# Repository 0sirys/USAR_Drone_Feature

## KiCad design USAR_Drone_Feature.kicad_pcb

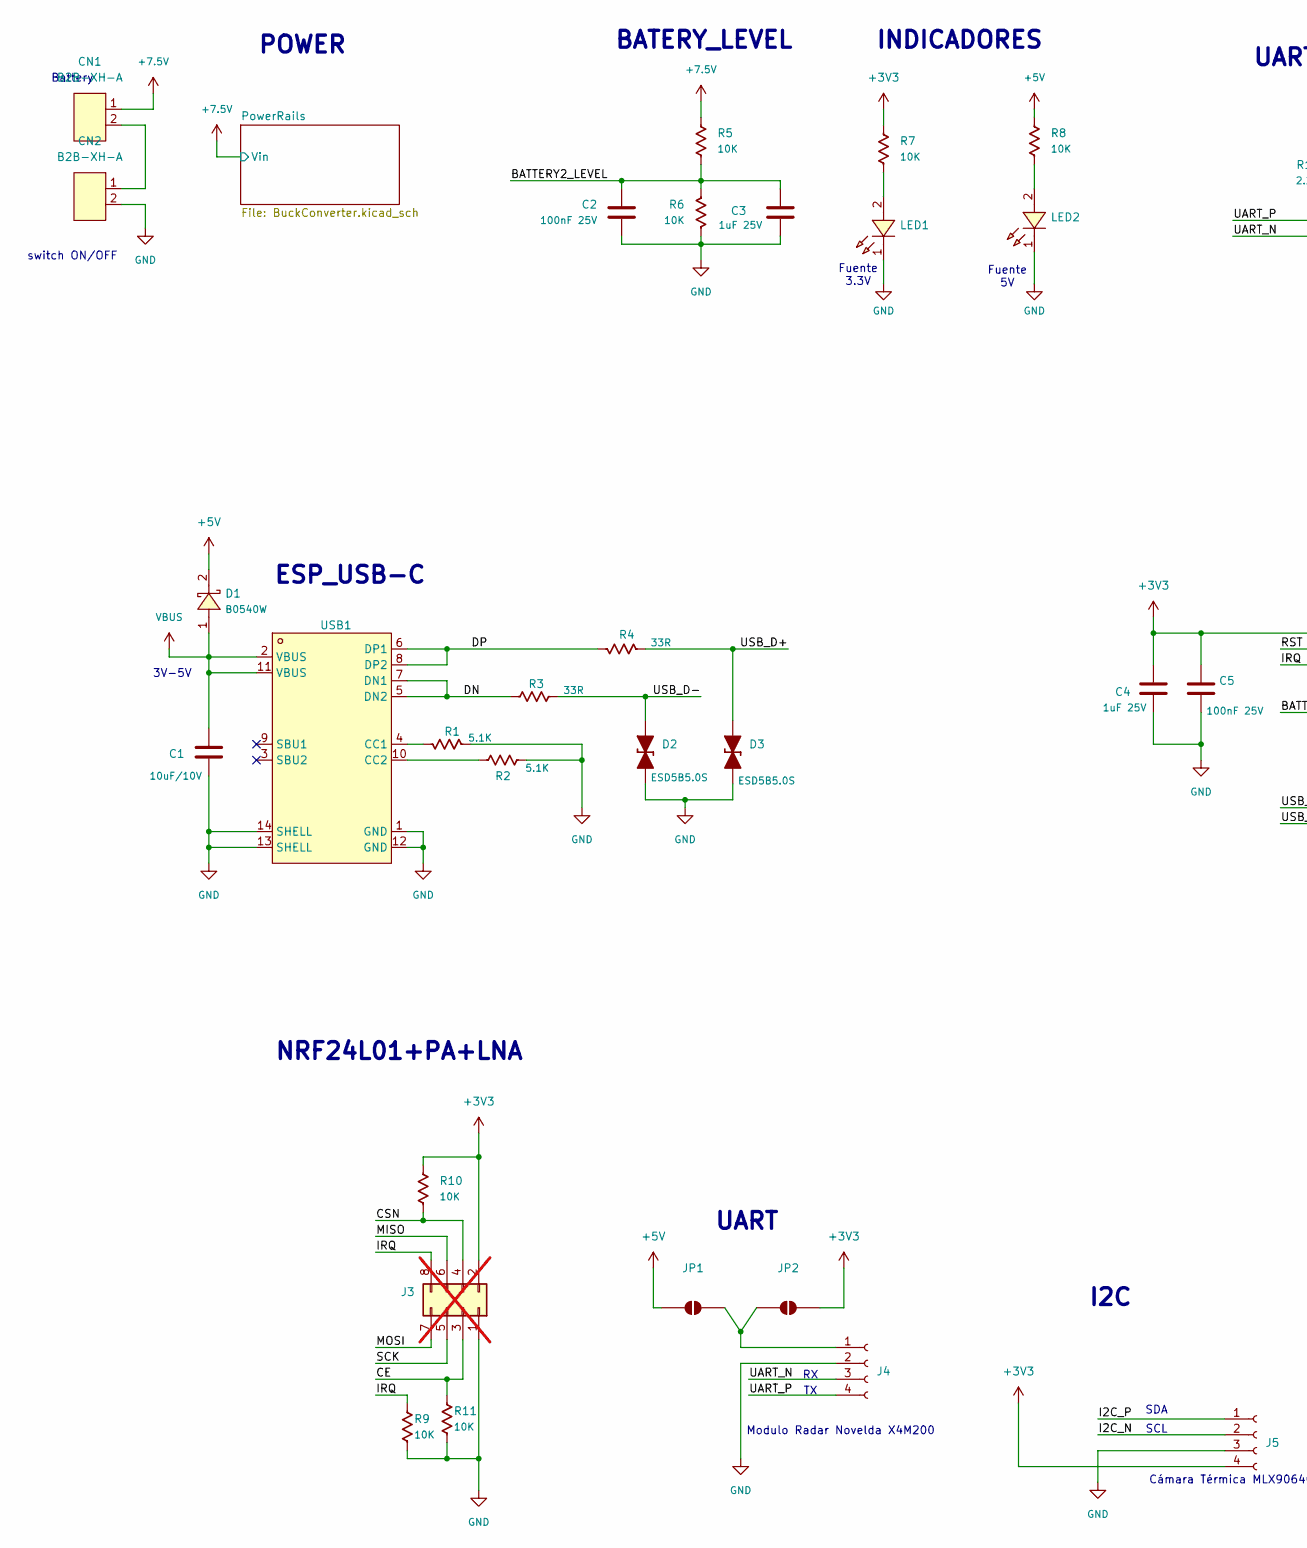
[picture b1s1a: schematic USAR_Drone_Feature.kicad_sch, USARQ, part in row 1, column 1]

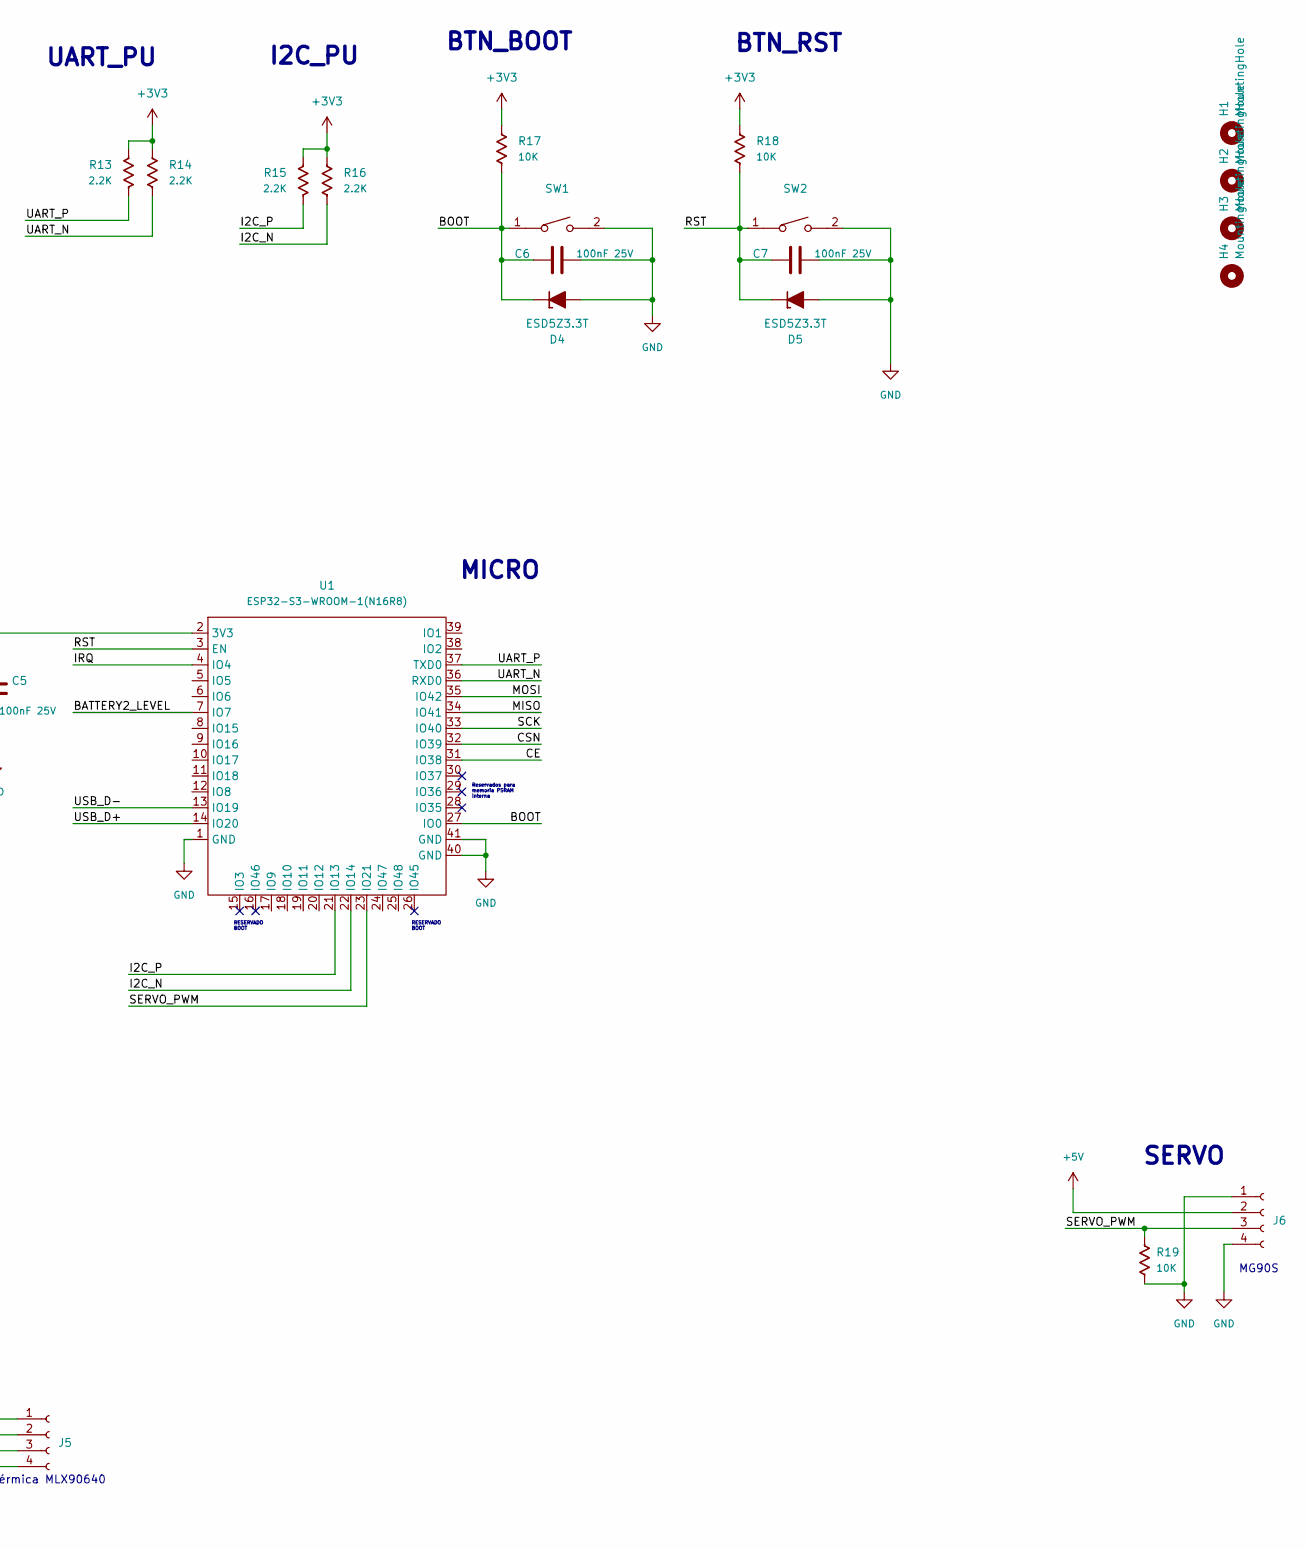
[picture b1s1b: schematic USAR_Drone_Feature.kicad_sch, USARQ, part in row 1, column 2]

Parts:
C1: 10uF/10V; C_0805_2012Metric; LCSC Part C326595
C2, C5, C6, C7: 100nF 25V; C_0603_1608Metric; LCSC Part C14663
C3, C4: 1uF 25V; C_0805_2012Metric; LCSC Part 5370002
CN1, CN2: B2B-XH-A; CONN-TH_B2B-XH-A-LF-SN; MPN B2B-XH-A(LF)(SN); LCSC Part C158012
D1: B0540W; SOD-123_L2.7-W1.6-LS3.7-FD; MPN B0540W; LCSC Part C7420325
D2, D3: ESD5B5.0S; D_SOD-523; LCSC Part C2936975
D4, D5: ESD5Z3.3T; D_SOD-523; LCSC Part C61148
H1, H2, H3, H4: MountingHole; MountingHole_2.5mm
J3: Conn_02x04_Odd_Even; PinHeader_2x04_P2.54mm_Vertical; not fitted
J4, J5, J6: Conn_01x04_Socket; CONN-TH_B4B-PH-K-S; LCSC Part C144395
JP1, JP2: SolderJumper_2_Open; Jumper_2_NO
LED1, LED2: XL-1608SURC-06; LED0603-RD_RED; MPN XL-1608SURC-06; LCSC Part C965799
R1, R2: 5.1K; R_0603_1608Metric; LCSC Part C125891
R3, R4: 33R; R_0603_1608Metric; LCSC Part C108407
R5, R6, R7, R8, R9, R10, R11, R17, R18, R19: 10K; R_0603_1608Metric; LCSC Part C860067
R13, R14, R15, R16: 2.2K; R_0603_1608Metric; LCSC Part C113303
SW1, SW2: TS-1088-AR02016; SW-SMD_L3.9-W3.0-P4.45; MPN TS-1088-AR02016; LCSC Part C720477
U1: ESP32-S3-WROOM-1(N16R8); WIRELM-SMD_ESP32-S3-WROOM-1; LCSC Part C2913202
USB1: TYPE-C 16PIN 2MD; USB-C-SMD_TYPE-C-6PIN-2MD-073; MPN TYPE-C 16PIN 2MD(073); LCSC Part C2765186

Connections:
+3V3: C4.1, C5.1, J3.2, J5.4, JP2.2 (B), R7.1, R10.1, R13.1, R14.1, R15.1, R16.1, R17.1, R18.1, U1.2 (3V3); also elsewhere on the board
+5V: D1.2, J6.2, JP1.1 (A), R8.1; also elsewhere on the board
+7.5V: CN1.1, R5.1; also elsewhere on the board
/BATTERY2_LEVEL: C2.1, C3.1, R5.2, R6.1, U1.7 (IO7)
/BOOT: C6.1, D4.1 (K), R17.2, SW1.1, U1.27 (IO0)
/CE: J3.3, R11.1, U1.31 (IO38)
/CSN: J3.4, R10.2, U1.32 (IO39)
/DN: R3.1, USB1.5 (DN2), USB1.7 (DN1)
/DP: R4.1, USB1.6 (DP1), USB1.8 (DP2)
/I2C_N: J5.2, R16.2, U1.22 (IO14)
/I2C_P: J5.1, R15.2, U1.21 (IO13)
/IRQ: J3.8, R9.1, U1.4 (IO4)
/MISO: J3.6, U1.34 (IO41)
/MOSI: J3.7, U1.35 (IO42)
/RST: C7.1, D5.1 (K), R18.2, SW2.1, U1.3 (EN)
/SCK: J3.5, U1.33 (IO40)
/SERVO_PWM: J6.3, R19.1, U1.23 (IO21)
/UART_N: J4.3, R14.2, U1.36 (RXD0)
/UART_P: J4.4, R13.2, U1.37 (TXD0)
/USB_D+: D3.2 (A), R4.2, U1.14 (IO20)
/USB_D-: D2.2 (A), R3.2, U1.13 (IO19)
GND: C1.2, C2.2, C3.2, C4.2, C5.2, C6.2, C7.2, CN2.2, D2.1 (K), D3.1 (K), D4.2 (A), D5.2 (A), J3.1, J4.2, J5.3, J6.1, J6.4, LED1.1, LED2.1, R1.2, R2.2, R6.2, R9.2, R11.2, R19.2, SW1.2, SW2.2, U1.1 (GND), U1.40 (GND), U1.41 (GND), USB1.1 (GND), USB1.12 (GND), USB1.13 (SHELL), USB1.14 (SHELL); also elsewhere on the board
unnamed: CN1.2, CN2.1
unnamed: J4.1, JP1.2 (B), JP2.1 (A)
unnamed: LED1.2, R7.2
unnamed: LED2.2, R8.2
unnamed: R1.1, USB1.4 (CC1)
unnamed: R2.1, USB1.10 (CC2)
VBUS: C1.1, D1.1, USB1.2 (VBUS), USB1.11 (VBUS)

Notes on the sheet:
MICRO
Fuente 3.3V
POWER
BATERY_LEVEL
SDA
MG90S
RESERVADO BOOT
SERVO
NRF24L01+PA+LNA
SCL
Battery
INDICADORES
BTN_BOOT
Cámara Térmica MLX90640
Modulo Radar Novelda X4M200
ESP_USB-C
I2C_PU
I2C
BTN_RST
UART
switch ON/OFF
Reservados para memoria PSRAM Interna
UART_PU
Fuente 5V
3V-5V

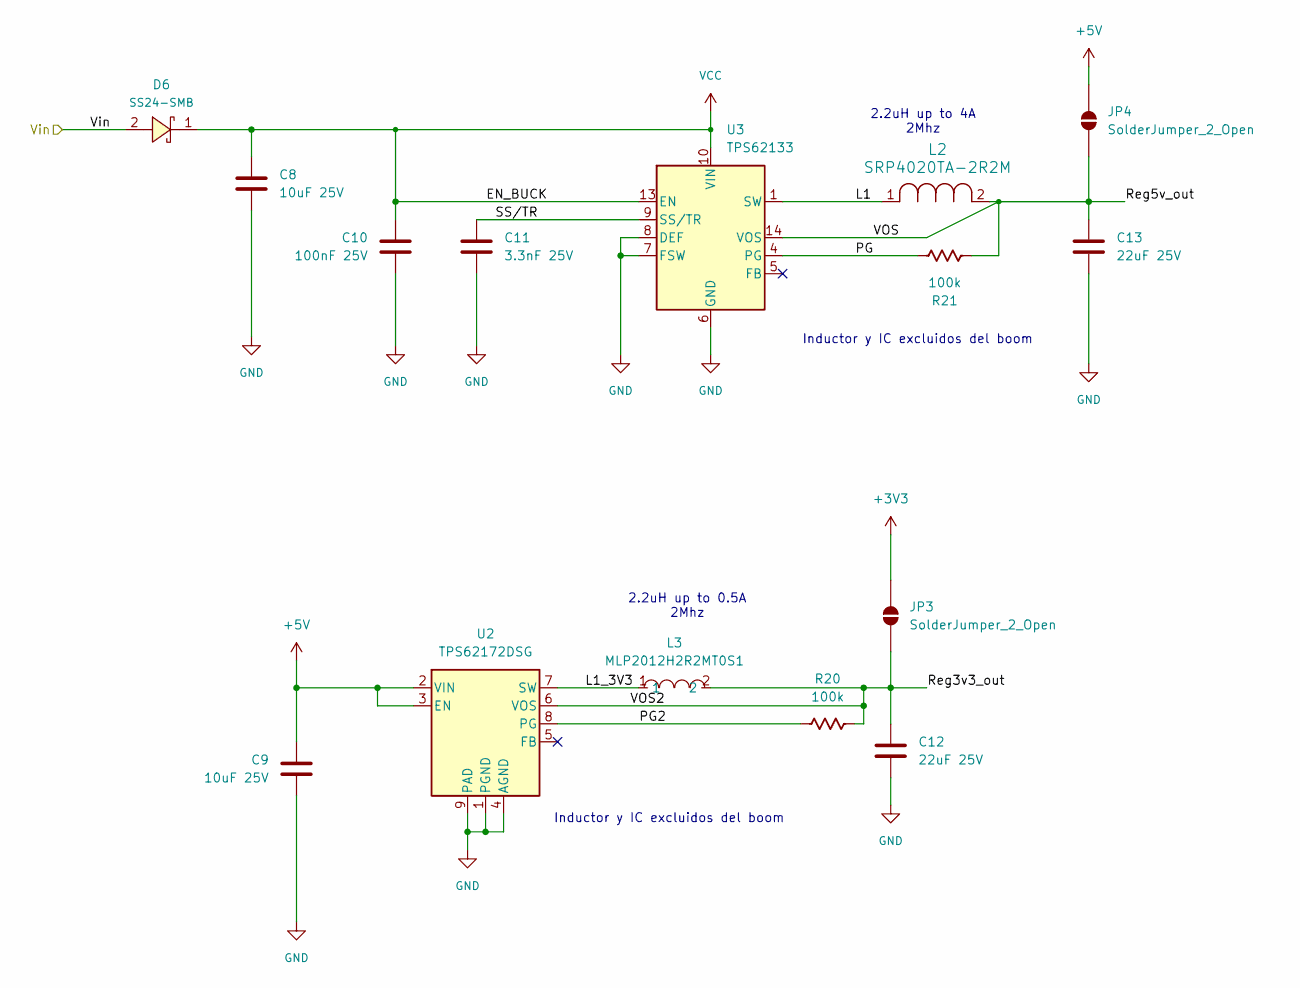
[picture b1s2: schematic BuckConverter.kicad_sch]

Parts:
C8, C9: 10uF 25V; C_1210_3225Metric; LCSC Part C577292
C10: 100nF 25V; C_0603_1608Metric; LCSC Part C14663
C11: 3.3nF 25V; C_0603_1608Metric; LCSC Part C107088
C12, C13: 22uF 25V; C_0805_2012Metric; LCSC Part C602037
D6: SS24-SMB; SMB_L4.3-W3.6-LS5.3-RD; MPN SS24-SMB; LCSC Part C908683
JP3, JP4: SolderJumper_2_Open; Jumper_2_NO
L2: SRP4020TA-2R2M; IND_SRP4020TA_BRN-L
L3: MLP2012H2R2MT0S1; L0805; MPN MLP2012H2R2MT0S1; LCSC Part C383369
R20, R21: 100k; R_0603_1608Metric; LCSC Part C122538
U2: TPS62172DSG; WSON-8-1EP_2x2mm_P0.5mm_EP0.9x1.6mm_ThermalVias
U3: TPS62133; VQFN-16-1EP_3x3mm_P0.5mm_EP1.68x1.68mm_ThermalVias

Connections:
+3V3: JP3.2 (B); also elsewhere on the board
+5V: C9.1, JP4.2 (B), U2.2 (VIN), U2.3 (EN); also elsewhere on the board
+7.5V: D6.2; also elsewhere on the board
/PowerRails/L1: L2.1, U3.1 (SW), U3.2 (SW), U3.3 (SW)
/PowerRails/L1_3V3: L3.1, U2.7 (SW)
/PowerRails/PG: R21.2, U3.4 (PG)
/PowerRails/PG2: R20.1, U2.8 (PG)
/PowerRails/Reg3v3_out: C12.1, JP3.1 (A), L3.2, R20.2, U2.6 (VOS)
/PowerRails/Reg5v_out: C13.1, JP4.1 (A), L2.2, R21.1, U3.14 (VOS)
/PowerRails/SS/TR: C11.2, U3.9 (SS/TR)
GND: C8.2, C9.2, C10.1, C11.1, C12.2, C13.2, U2.1 (PGND), U2.4 (AGND), U2.9 (PAD), U3.6 (GND), U3.7 (FSW), U3.8 (DEF), U3.15 (GND), U3.16 (GND), U3.17 (GND); also elsewhere on the board
VCC: C8.1, C10.2, D6.1, U3.10 (VIN), U3.11 (VIN), U3.12 (VIN), U3.13 (EN)

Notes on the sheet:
2.2uH up to 0.5A 2Mhz
Inductor y IC excluidos del boom
2.2uH up to 4A 2Mhz

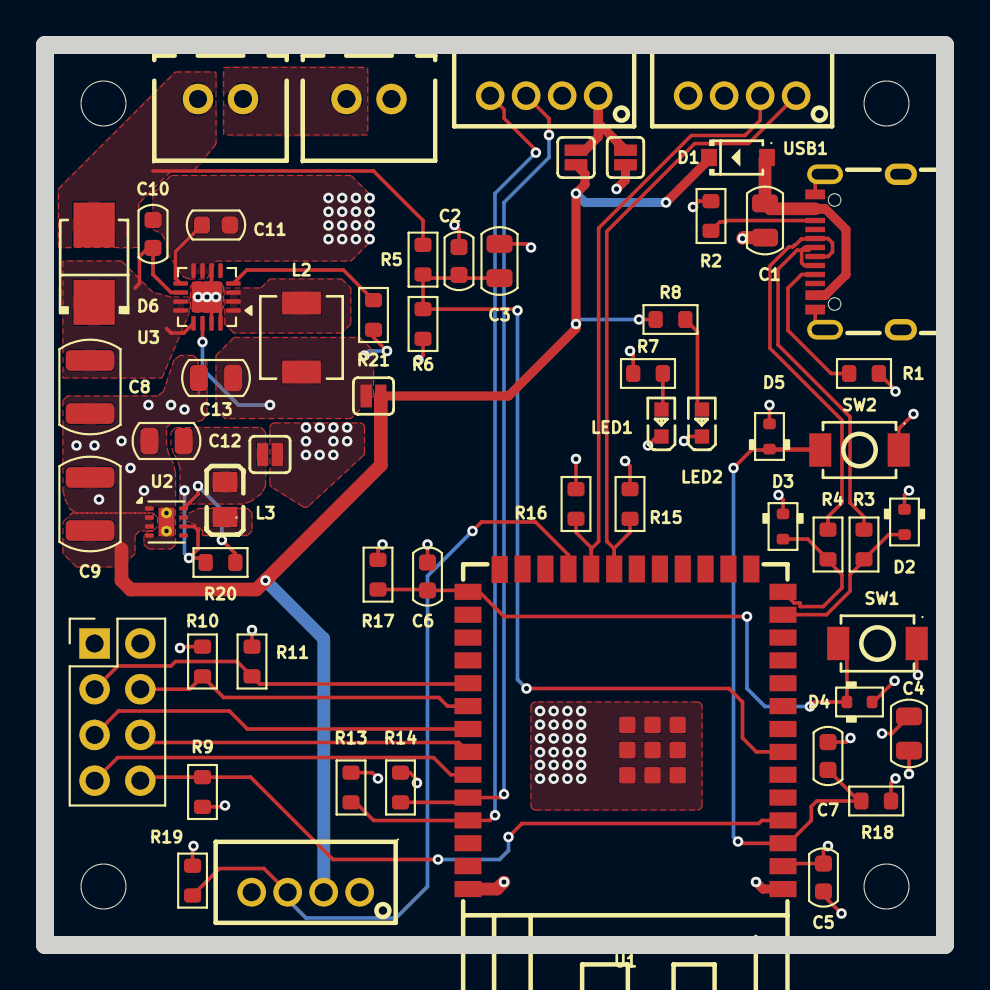
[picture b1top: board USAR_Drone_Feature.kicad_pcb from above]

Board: 4 copper layers, 50.0 x 50.0 mm, 63 parts (0 on the bottom side), 37 nets.

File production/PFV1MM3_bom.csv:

Designator,Footprint,Quantity,Value,LCSC Part #
C1,0805,1,10uF/10V,C326595
"C10, C2, C5, C6, C7",0603,5,100nF 25V,C14663
C11,0603,1,3.3nF 25V,C107088
"C12, C13",0805,2,22uF 25V,C602037
"C3, C4",0805,2,1uF 25V,5370002
"C8, C9",1210,2,10uF 25V,C577292
"CN1, CN2",CONN-TH_B2B-XH-A-LF-SN,2,B2B-XH-A,C158012
D1,SOD-123_L2.7-W1.6-LS3.7-FD,1,B0540W,C7420325
"D2, D3",D_SOD-523,2,ESD5B5.0S,C2936975
"D4, D5",D_SOD-523,2,ESD5Z3.3T,C61148
D6,SMB_L4.3-W3.6-LS5.3-RD,1,SS24-SMB,C908683
"J4, J5, J6",CONN-TH_B4B-PH-K-S,3,Conn_01x04_Socket,C144395
L3,L0805,1,MLP2012H2R2MT0S1,C383369
"LED1, LED2",LED0603-RD_RED,2,XL-1608SURC-06,C965799
"R1, R2",0603,2,5.1K,C125891
"R10, R11, R17, R18, R19, R5, R6, R7, R8, R9",0603,10,10K,C860067
"R13, R14, R15, R16",0603,4,2.2K,C113303
"R20, R21",0603,2,100k,C122538
"R3, R4",0603,2,33R,C108407
"SW1, SW2",SW-SMD_L3.9-W3.0-P4.45,2,TS-1088-AR02016,C720477
U1,WIRELM-SMD_ESP32-S3-WROOM-1,1,ESP32-S3-WROOM-1(N16R8),C2913202
USB1,USB-C-SMD_TYPE-C-6PIN-2MD-073,1,TYPE-C 16PIN 2MD,C2765186

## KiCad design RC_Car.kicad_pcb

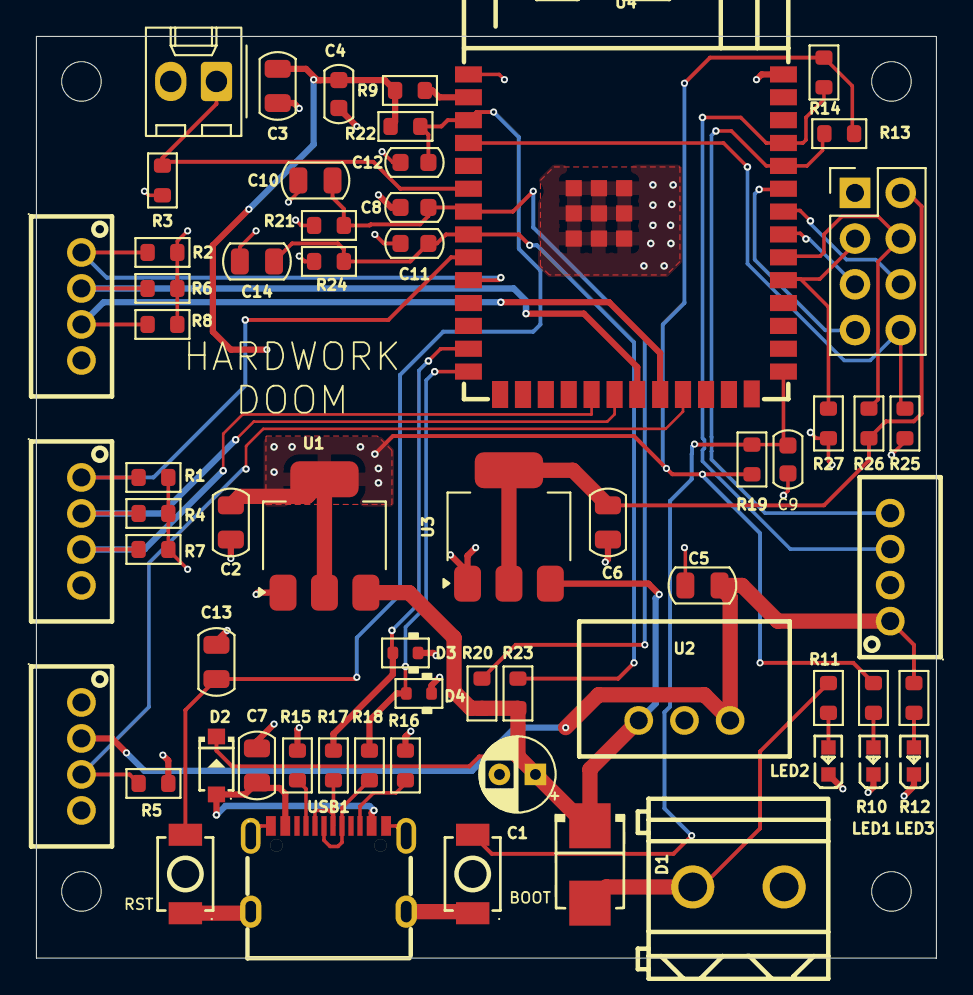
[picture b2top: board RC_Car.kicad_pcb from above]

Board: 2 copper layers, 50.0 x 51.2 mm, 66 parts (0 on the bottom side), 37 nets.

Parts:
C1: 100uF; CP_Radial_D4.0mm_P2.00mm
C2, C5, C6, C7: 10uF/10V; C_0805_2012Metric
C3, C10, C13: 1uF/10V; C_0805_2012Metric
C4, C8, C9, C11, C12: 0.1uF/10V; C_0603_1608Metric
C14: 1uF; C_0805_2012Metric
D1: SS24-SMB; SMB_L4.3-W3.6-LS5.3-RD
D2: B0540W; SOD-123_L2.7-W1.6-LS3.7-FD
D3, D4: ESD5B5.0S; D_SOD-523
H1, H2, H3, H4: MountingHole; MountingHole_2.2mm_M2_DIN965
J1: DB128L-5.08-2P-BK-S; CONN-TH_2P-P5.08_DB128L-5.08-2P-BK-S
J2: Conn_01x02_Socket; Molex_KK-254_AE-6410-02A_1x02_P2.54mm_Vertical
J3, J4, J5, J6: Conn_01x04_Socket; CONN-TH_B4B-PH-K-S
J7: Conn_02x04_Odd_Even; PinHeader_2x04_P2.54mm_Vertical
LED1, LED2, LED3: XL-1608SURC-06; LED0603-RD_RED
R1, R2, R3, R4, R5, R6, R7, R8, R10, R11, R12, R19, R20, R21, R22, R23, R24, R25, R26, R27: 10K; R_0603_1608Metric
R9: 0(1%); R_0603_1608Metric
R13, R14: 2.2K; R_0603_1608Metric
R15, R16: 5.1K; R_0603_1608Metric
R17, R18: 33R; R_0603_1608Metric
SW1, SW2: TS-1088-AR02016; SW-SMD_L3.9-W3.0-P4.45
U1, U3: AMS1117-3.3; SOT-223-3_TabPin2
U2: TSR 1-2450_C6886877; PWRM-TH_L11.7-W7.5_TSR1-2450
U4: ESP32-S3-WROOM-1(N16R8); WIRELM-SMD_ESP32-S3-WROOM-1
USB1: TYPE-C 16PIN 2MD; USB-C-SMD_TYPE-C-6PIN-2MD-073

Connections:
+3.3V: C2.1, C3.1, C4.1, R9.1, R10.1, R13.1, R14.1, R19.1, R22.1, U1.2 (VO)
+3.3V_RF: C6.1, J7.2, R26.1, U3.2 (VO)
+5V: C5.1, J4.2, J6.1, R12.1, U2.3 (+Vout)
+7.5V: D1.2, J1.1, R11.1
/BATTERY1_LEVEL: C11.1, C14.1, R23.2, R24.1, U4.8 (IO15)
/BATTERY2_LEVEL: C8.1, C10.1, R20.2, R21.1, U4.7 (IO7)
/BOOT: C9.1, R19.2, SW1.1, U4.27 (IO0)
/CE: J7.3, R27.1, U4.31 (IO38)
/CSN: J7.4, R26.2, U4.32 (IO39)
/IRQ: J7.8, R25.1, U4.4 (IO4)
/M1_DIR_L: J3.2, R4.1, U4.20 (IO12)
/M1_DIR_R: J3.3, R7.1, U4.19 (IO11)
/M1_PWM: J3.1, R1.1, U4.9 (IO16)
/M2_DIR_L: J5.2, R6.1, U4.21 (IO13)
/M2_DIR_R: J5.3, R8.1, U4.22 (IO14)
/M2_PWM: J5.1, R2.1, U4.10 (IO17)
/MISO: J7.6, U4.34 (IO41)
/MOSI: J7.7, U4.35 (IO42)
/OSD_PWM: J2.1, R3.1, U4.6 (IO6)
/RST: C12.1, C13.1, R22.2, SW2.1, U4.3 (EN)
/SCK: J7.5, U4.33 (IO40)
/SERVO_PWM: J4.3, R5.1, U4.23 (IO21)
/UART_RX0: J6.4, R13.2, U4.36 (RXD0)
/UART_TX0: J6.3, R14.2, U4.37 (TXD0)
/USB_D+: D4.2 (A), R18.2, U4.14 (IO20)
/USB_D-: D3.2 (A), R17.2, U4.13 (IO19)
ESP_3.3V: R9.2, U4.2 (3V3)
GND: C1.2, C2.2, C3.2, C4.2, C5.2, C6.2, C7.2, C8.2, C9.2, C10.2, C11.2, C12.2, C13.2, C14.2, D3.1 (K), D4.1 (K), J1.2, J2.2, J3.4, J4.1, J4.4, J5.4, J6.2, J7.1, LED1.1, LED2.1, LED3.1, R1.2, R2.2, R3.2, R4.2, R5.2, R6.2, R7.2, R8.2, R15.2, R16.2, R21.2, R24.2, R25.2, R27.2, SW1.2, SW2.2, U1.1 (GND), U2.2 (GND), U3.1 (GND), U4.1 (GND), U4.40 (GND), U4.41 (GND), USB1.1 (GND), USB1.12 (GND), USB1.13 (SHELL), USB1.14 (SHELL)
unnamed: LED1.2, R10.2
unnamed: LED2.2, R11.2
unnamed: LED3.2, R12.2
unnamed: R15.1, USB1.4 (CC1)
unnamed: R16.1, USB1.10 (CC2)
unnamed: R17.1, USB1.5 (DN2), USB1.7 (DN1)
unnamed: R18.1, USB1.6 (DP1), USB1.8 (DP2)
VBUS: C7.1, D2.1, USB1.2 (VBUS), USB1.11 (VBUS)
VCC: C1.1, D1.1, D2.2, R20.1, R23.1, U1.3 (VI), U2.1 (+Vin), U3.3 (VI)

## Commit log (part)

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2026-06-17 Primer commit
